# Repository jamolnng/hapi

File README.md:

# hapi
Source code for Holographic Aerosol Particle Imager (HAPI)

Instrument to image large aerosol particles from an unmanned aerial vehicle

Advising Professor: Matthew J. Berg, Kansas State University

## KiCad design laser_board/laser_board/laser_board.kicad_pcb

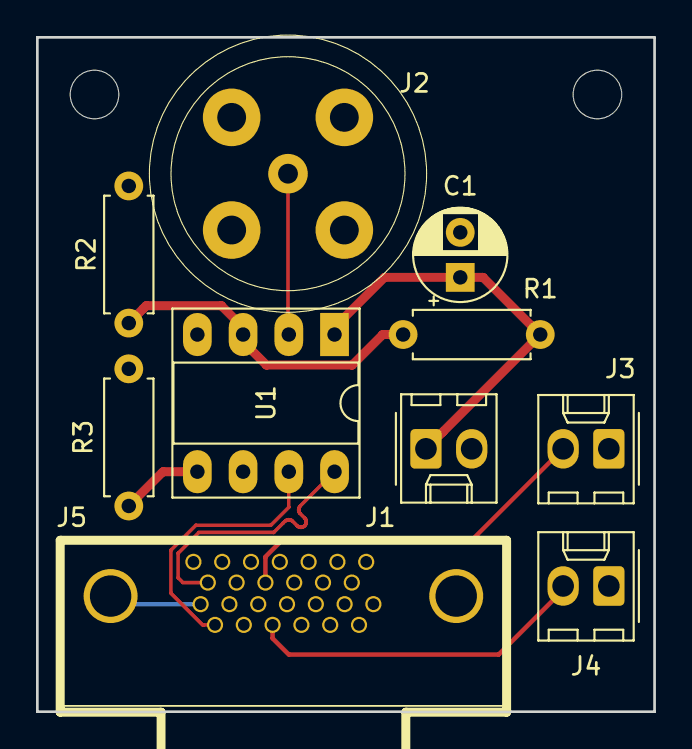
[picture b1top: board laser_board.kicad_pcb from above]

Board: 2 copper layers, 34.3 x 37.5 mm, 10 parts (0 on the bottom side), 9 nets.

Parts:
C1: CP1; CP_Radial_D5.0mm_P2.50mm
J1: Power; Molex_KK-254_AE-6410-02A_1x02_P2.54mm_Vertical
J2: Trigger In; te_conn_bnc_1634503
J3: Laser Ready; Molex_KK-254_AE-6410-02A_1x02_P2.54mm_Vertical
J4: Laser Fault; Molex_KK-254_AE-6410-02A_1x02_P2.54mm_Vertical
J5: 12226-5150-00FR; 3mtm-shrunk-delta-ribbon-sdr-connectors-122-series-ts2124
R1, R2, R3: 10k; R_Axial_DIN0207_L6.3mm_D2.5mm_P7.62mm_Horizontal
U1: AD8561; DIP-8_W7.62mm_Socket_LongPads

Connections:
DP_N: J5.12, U1.8
DP_P: J5.25, U1.7
GND: C1.2, J1.2, J2.2, J3.1, J4.1, J5.2, J5.3, J5.15, J5.16, J5.26, J5.Shell, R2.2, R3.1, U1.4, U1.6
unnamed: J2.1, U1.2
unnamed: J3.2, J5.8
unnamed: J4.2, J5.21
unnamed: R1.1, R2.1, U1.3
unnamed: R3.2, U1.5
VCC: C1.1, J1.1, R1.2, U1.1

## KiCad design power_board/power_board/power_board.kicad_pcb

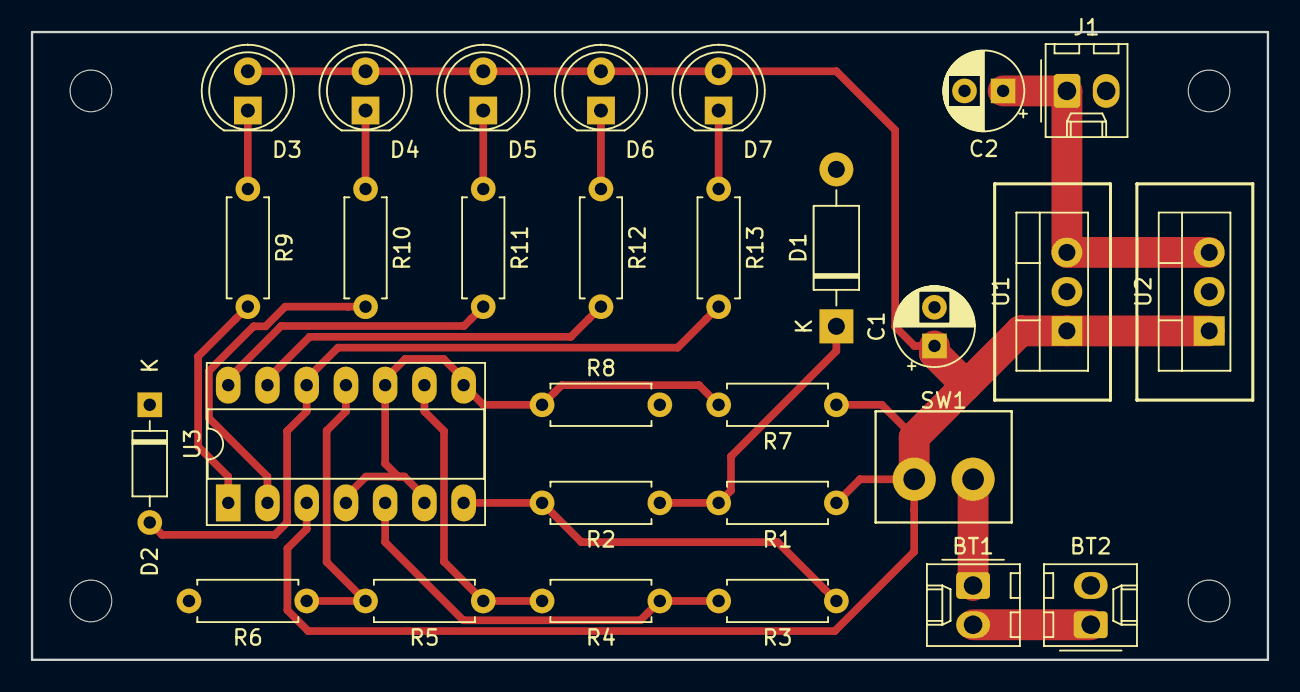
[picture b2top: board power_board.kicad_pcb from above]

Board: 2 copper layers, 80.0 x 40.6 mm, 29 parts (0 on the bottom side), 21 nets.

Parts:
BT1, BT2: Battery; Molex_KK-254_AE-6410-02A_1x02_P2.54mm_Vertical
C1, C2: 0.1uF; CP_Radial_D5.0mm_P2.50mm
D1: 1N4735A; D_DO-41_SOD81_P10.16mm_Horizontal
D2: 1N4148; D_DO-35_SOD27_P7.62mm_Horizontal
D3, D4, D5, D6, D7: LED; LED_D5.0mm
J1: Conn_01x02_Female; Molex_KK-254_AE-6410-02A_1x02_P2.54mm_Vertical
R1: 1k; R_Axial_DIN0207_L6.3mm_D2.5mm_P7.62mm_Horizontal
R2, R3, R4, R5, R6: R; R_Axial_DIN0207_L6.3mm_D2.5mm_P7.62mm_Horizontal
R7: 16k; R_Axial_DIN0207_L6.3mm_D2.5mm_P7.62mm_Horizontal
R8: 6.2k; R_Axial_DIN0207_L6.3mm_D2.5mm_P7.62mm_Horizontal
R9, R10, R11, R12, R13: 2.2k; R_Axial_DIN0207_L6.3mm_D2.5mm_P7.62mm_Horizontal
SW1: SW_SPST; amphenol_term_block_hdr_2pos_vert_3.81mm
U1, U2: LM7812_TO220; TO-220-3_Vertical
U3: LM339; DIP-14_W7.62mm_Socket_LongPads

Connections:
GND: BT2.2, C1.2, C2.2, D1.2, D2.1, J1.2, R6.2, R8.2, U1.2, U2.2
unnamed: BT1.1, SW1.2
unnamed: BT1.2, BT2.1
unnamed: C2.1, J1.1, U1.3, U2.3
unnamed: D1.1, R1.2, R2.1
unnamed: D2.2, R13.2, U3.12
unnamed: D3.1, R9.1
unnamed: D4.1, R10.1
unnamed: D5.1, R11.1
unnamed: D6.1, R12.1
unnamed: D7.1, R13.1
unnamed: R2.2, R3.1, U3.7
unnamed: R3.2, R4.1, U3.5
unnamed: R4.2, R5.1, U3.9
unnamed: R5.2, R6.1, U3.11
unnamed: R7.2, R8.1, U3.4, U3.6, U3.8, U3.10
unnamed: R9.2, U3.1
unnamed: R10.2, U3.2
unnamed: R11.2, U3.14
unnamed: R12.2, U3.13
VCC: C1.1, D3.2, D4.2, D5.2, D6.2, D7.2, R1.1, R7.1, SW1.1, U1.1, U2.1, U3.3

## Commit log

2018-10-27 cmake
2018-10-27 changed binary output directory
2018-10-27 added install
2018-10-27 include fix
2018-10-27 check if config exists
2018-10-27 added default values and time formatting
2018-10-27 gitignore
2018-10-27 google code style
2018-10-27 added done pin
2018-10-27 comments and system init fixes
2018-10-27 added done pin prompt
2018-10-29 added program macro
2018-10-31 setup file complete
2018-10-31 cleanup cmakelist.txt
2018-10-31 rework usb camera interface
2018-10-31 format setup for readability
2018-11-01 minor
2018-11-02 0.0.1 working
2018-11-02 set usbfs memory
2018-11-02 added functions to set gain and exposure settings
2018-11-02 changed line endings
2018-11-02 set exposure and gain
2018-11-02 disable color processing
2018-11-02 fixed service
2018-11-06 finally working
2018-11-06 added board reset
2018-11-06 logging
2018-11-07 added spinnaker headers
2018-11-07 Switch to QuickSpin API
2018-11-07 changed include guard
2018-11-07 redid logging
2018-11-07 create thumbnails
2018-11-07 hologram viewer
2018-11-07 made sure everything works
2018-11-08 fixed camera scope
2018-11-09 moved things to functions
2018-11-13 added pmt code
2018-11-13 add log append
2018-11-16 trigger config
2018-11-17 fixed append
2018-11-17 changed pin delay
2018-11-17 fixed cpp issue
2018-11-17 fixed stoi issue with b
2018-11-19 added argument parser
2018-11-20 add software trigger function
    not implemented
2018-11-20 add run modes
2018-11-20 changed config
2018-12-06 disable service
2018-12-06 added different trigger sources
2018-12-06 added saving
2018-12-08 moved routines to their own files
    cleans up main.cpp
2018-12-08 created pmt calibration code
2018-12-08 pmt calibrate
2018-12-08 fixed acquisition
2018-12-08 create symlink to last image
2018-12-08 fixes
2018-12-10 build passing
2018-12-10 pmt calibration success
2018-12-10 fixed acquisition links
2018-12-10 added long name for argparse
2018-12-10 convert last thumb to png
2018-12-10 hapiweb
2018-12-11 ran cppclean
2018-12-11 long arguments
2018-12-13 update pmt calibration logging
2018-12-17 pmt calibration fixes
2018-12-18 hardware
2018-12-18 laser board
2018-12-19 ground plane capacitance
2018-12-20 board drawings
2019-03-08 lots of updates that never got pushed
2019-03-09 cleanup
2019-03-14 moved exec to os_utils
2019-03-14 added alignment mode
2019-03-14 fix obis source type query
2019-03-14 minor fixes
2019-03-15 fix startup script
2019-03-15 cw and align modes
2019-03-28 ubuntu
2019-04-23 change directories
2019-04-23 binary search calibration
2019-04-23 Matched config with documentation
2019-05-07 directory fixes
2019-05-07 Force hardware triggering
2019-05-07 Set pixel format to 12 bit
2019-05-07 documentation
2019-05-07 update argparse
2019-05-07 fixed binary search
2019-05-07 moved config saving
2019-05-11 added support for negative arguments
2019-05-11 added config/cmd line threshold offset
2019-05-11 added global run number
2019-05-11 update filesystem include
2019-05-12 create run number file if it doesn't exist
